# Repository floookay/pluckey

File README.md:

the pluckey is an ergodox like split keyboard with more pronounced columnal stagger and a vertical space key.  

I took inspiration from splitkbs Kyria and bishborias Ergodox design.

## layout

The following physical layouts are supported:  
  
And this is the default keymap as of now:  
  
[Keyboard-Layout-Editor](http://www.keyboard-layout-editor.com/#/gists/13c9d00bd0c0c9e3fe3b3d8d98672ef9) [(raw)](https://gist.github.com/floookay/13c9d00bd0c0c9e3fe3b3d8d98672ef9)

## pcb

The pcb is reversible and supports pcb mount MX style switches.  
It was designed using KiCAD and the following external libaries: [keebio-parts](https://github.com/keebio/Keebio-Parts.pretty) and [foostans kbd library](https://github.com/foostan/kbd)  
In order to assemble a pair you'll need the following hardware:

| amount | part                 | description             |
|--------|----------------------|-------------------------|
| 66/68  | key switches         | MX style                |
| 66/68  | diodes               | SMD or THT 1N4148(W)    |
| 2      | mini USB ports       | MX-54819-0519           |
| 2      | TRRS jacks           |                         |
| 2      | tact switch          |                         |
| 2      | pro micros           |                         |
| 2      | micro usb connectors | or two micro usb cables |
| 8      | short wires          |                         |

Additionally I'd recommend getting a pair of hotswapable headers for both pro micros.

**assembly:**  
Start by soldering the diodes, the headers, trrs jack and the mini usb port to the same side of the pcb. Make sure to clip the pins beforehand so they're flush on the other side.  
Now you can align your plate and solder in the switches.  
Plug the micro usb connector into the pro micro and align it according to the pinout on the solder mask. Depending on which headers you chose you might want to add electrical tape to the pro micro that's upside down so it doesnt touch the switch pins. Also nothe that you might have to solder on the controller at an angle if you're going with the default headers in order to be able to plug in the usb cable.  
Solder the wires to the micro usb connector (or cut open your existing cables) and solder the other side to the port headers according to the pinout on the solder mask.

<details>
<summary>more pictures</summary>

</details>
<br>

## case

### monolith

The monolith case is a tray mounted design and 3d printable in two pieces: case and (optional) plate  
It was designed using FreeCAD (and some SolidPython until it got too complex for me) so please feel free to configure the case to your liking. It's fairly parametric set up so depending on what you want to achieve you'll have a few starting points.
In order to assemble the case you'll need the following additional hardware:

| amount | part                 |
|--------|----------------------|
| 8      | M2 4mm screws        |
| 8      | M2 4mm spacers       |
| 8+     | rubber feet          |

**assembly:**  
After you soldered the PCB you can assemble the case. At first you're going to have to merge the spacers with the posts of the case. To do this heat up your soldering iron, position a spacer with a tweezer and press the spacer down with the tip of your soldering iron (make sure it's clean before this step). Do this with the other spacers, align the plate and pcb and fixate it with the screws. Lastly you can add the rubber feet according to your liking.

<details>
<summary>more pictures</summary>

</details>
<br>

### skeleton

The skeleton case is a simple open case for the pluckey pcb.  
The FreeCAD models are included in case you want to adjust the angle for example.  
All you need to do to assemble this case is to clip in the PCB. All you need to do to assemble this case is to clip in the PCB. If you're using encoders you'll have to cut the pins flush.

<details>
<summary>more pictures</summary>

</details>
<br>

### sandwich

The sandwich case is a laser cut acrylic case for the pluckey pcb from 3mm thick layers.
I also built this with FreeCAD so feel free to adjust. The kerf of the files is set to 0.2mm so you might need to adjust that.

| amount | part                                            |
|--------|-------------------------------------------------|
| 32     | M2 5+mm screws                                  |
| 1      | set of cylindrical M2 standoffs (male + female) |
| 4      | diode legs                                      |
| 8+     | rubber feet                                     |

**assembly:**  
After you soldered the components to the PCB you can start soldering the switches with the plate in between. If you want to use a rotary encoder you'll have to enlargen the hole slightly with a dremel to fit its legs. As this is a 3mm plate I like to put small strips of cellular rubber vertically along the columns between the pcb and plate next to the switches. This prevents the switches from popping out of the plate. After you soldered the plate you can put screws in the top layer and gradually add the other layers, spacers and diode legs as soon as they fit. Use the male and female standoffs to create larger larger standoffs that fit each hole height (for the exact length opne „more pictures“). Lastly add the rubber feet, make sure that you place them at the same distance from the edge of each step.

<details>
<summary>more pictures</summary>

</details>
<br>

## plate

If you want to print and use a plate I'd suggest you print the tolerance tester first (and maybe decrease the tolerances a bit).  
After you know the right margin for your printer you can adjust it in the plate model and export your plate in the desired layout.

## firmware

[QMK firmware](https://github.com/floookay/qmk_firmware/tree/master/keyboards/pluckey)

Compiling the keyboard (after setting up your build environment):

    make pluckey:default

Flashing the firmware:

    make pluckey:default:flash

## misc

> What where your goals behind designing this keyboard?

One thing I wanted to improve/avoid were keys that needed to be stabilized but at the same time have wider space keys to rest my thumbs on.

Another thing I wanted to achieve with this design was to be fairly flexible in terms of keycaps that can be used.  
Personally, I like the wider ergodox style modifier keys but keycap compability is unfortunatelly not that great beyond blank uniform caps.  
That's why I made the PCB compatible with all 1u keycaps that are offered in ortho keycap sets.

> What's next?

~~An acrylic sandwich-style case variants.~~  
I'm also thinking about making a pcb variant for low profile Choc switches with choc spacing.  

> What's the story behind the name?

I named the keyboard Pluckey after one of my favorite Animal Crossing villagers „Plucky“. The first letter of the logo represents Pluckys eye.

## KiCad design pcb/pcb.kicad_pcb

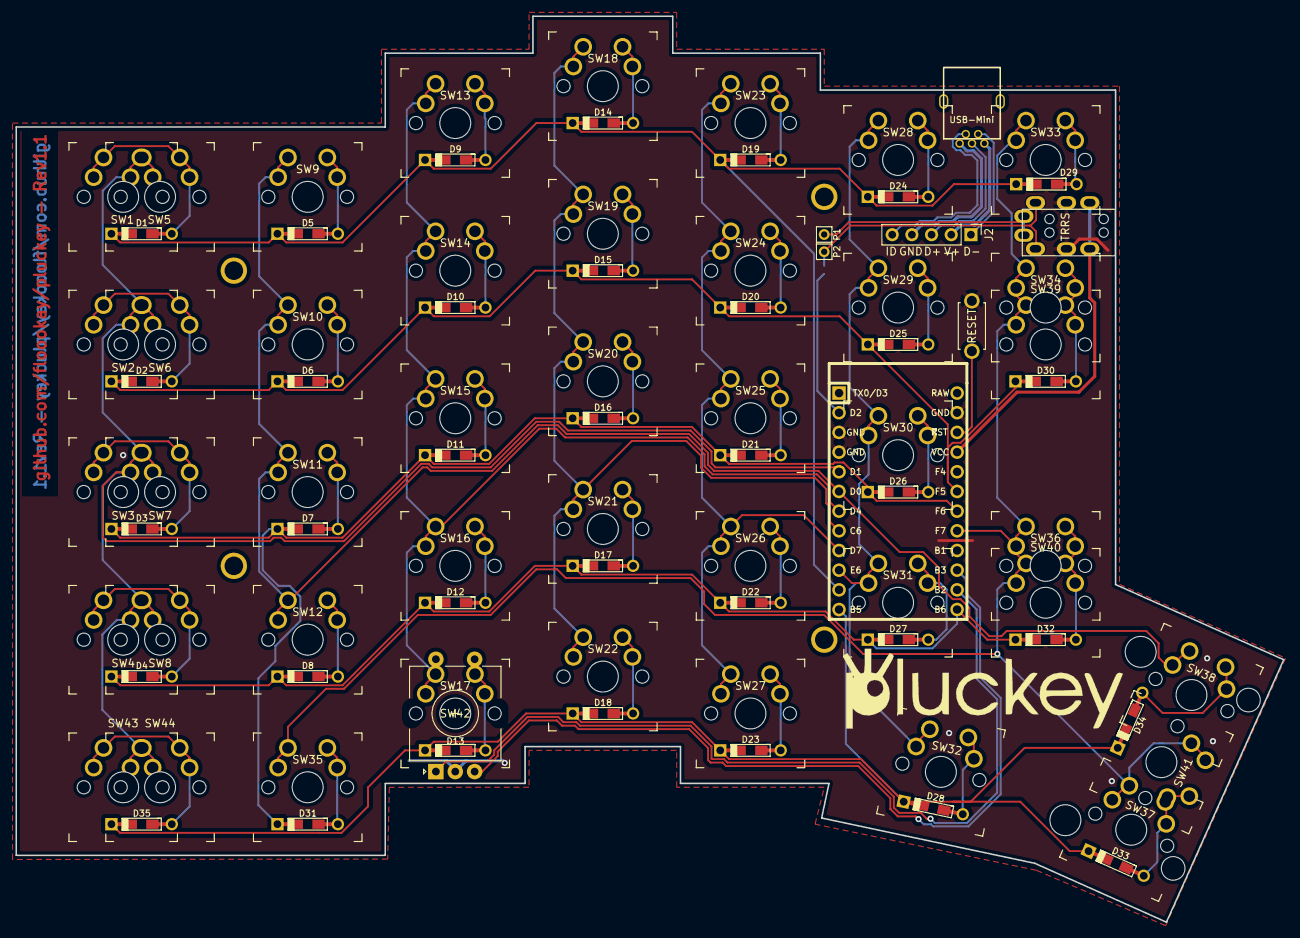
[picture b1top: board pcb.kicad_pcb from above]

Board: 2 copper layers, 163.6 x 116.9 mm, 91 parts (1 on the bottom side), 60 nets.

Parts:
D1, D2, D3, D4, D5, D6, D7, D8, D9, D10, D11, D12, D13, D14, D15, D16, D17, D18, D19, D20, D21, D22, D23, D24, D25, D26, D27, D28, D29, D30, D31, D32, D33, D34, D35: D; Diode-dual
H1, H2, H3, H4: MountingHole; m2.4_hole_plated
J1: USB-Mini; USB-Mini-B_2leg
J2: Conn_01x05; PinHeader_1x05_P2.54mm_Vertical
JP1: Jumper; JPC2
P1: i2c-pin1; 1pin_conn
P2: i2c-pin2; 1pin_conn
RSW1: SW_PUSH; ResetSW
SW1, SW2, SW3, SW4, SW5, SW6, SW7, SW8, SW9, SW10, SW11, SW12, SW13, SW14, SW15, SW16, SW17, SW18, SW19, SW20, SW21, SW22, SW23, SW24, SW25, SW26, SW27, SW28, SW29, SW30, SW31, SW32, SW33, SW34, SW35, SW36, SW37, SW38, SW39, SW40, SW41, SW43, SW44: SW_Push; SW_MX_reversible
SW42: Rotary_Encoder_Switch; RotaryEncoder_Alps_EC11E-Switch_Vertical_H20mm
U1: ProMicro; ArduinoProMicro
U2: TRRS; MJ-4PP-9

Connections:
/col0: SW1.2, SW2.2, SW3.2, SW4.2, SW5.1, SW6.1, SW7.1, SW8.1, SW43.2, SW44.1, U1.5 (2/PD1)
/col1: SW9.1, SW10.1, SW11.1, SW12.1, SW38.1, U1.6 (3/PD0)
/col2: SW13.1, SW14.1, SW15.1, SW16.1, SW17.1, SW42.S2, U1.7 (4/PD4)
/col3: SW18.1, SW19.1, SW20.1, SW21.1, SW22.1, U1.8 (5/PC6)
/col4: SW23.1, SW24.1, SW25.1, SW26.1, SW27.1, U1.9 (6/PD7)
/col5: SW28.1, SW29.1, SW30.1, SW31.1, SW32.1, U1.10 (7/PE6)
/col6: SW33.1, SW34.1, SW35.1, SW36.1, SW37.1, SW39.1, SW40.1, SW41.1, U1.17 (A0/PF7)
/data: JP1.1, U1.2 (RX1/PD2)
/re0: SW42.B, U1.15 (14/PB3)
/re1: SW42.A, U1.14 (16/PB2)
/reset: RSW1.1, U1.22 (RST)
/row0: D1.1 (K), D5.1 (K), D9.1 (K), D14.1 (K), D19.1 (K), D24.1 (K), D29.1 (K), U1.11 (8/PB4)
/row1: D2.1 (K), D6.1 (K), D10.1 (K), D15.1 (K), D20.1 (K), D25.1 (K), D30.1 (K), U1.19 (A2/PF5)
/row2: D3.1 (K), D7.1 (K), D11.1 (K), D16.1 (K), D21.1 (K), D26.1 (K), D31.1 (K), U1.18 (A1/PF6)
/row3: D4.1 (K), D8.1 (K), D12.1 (K), D17.1 (K), D22.1 (K), D27.1 (K), D32.1 (K), U1.13 (10/PB6)
/row4: D13.1 (K), D18.1 (K), D23.1 (K), D28.1 (K), D33.1 (K), D34.1 (K), D35.1 (K), U1.12 (9/PB5)
GND: RSW1.2, SW42.C, U1.3 (GND), U1.4 (GND), U1.23 (GND), U2.3 (RING1)
unnamed: D1.2 (A), SW1.1, SW5.2
unnamed: D2.2 (A), SW2.1, SW6.2
unnamed: D3.2 (A), SW3.1, SW7.2
unnamed: D4.2 (A), SW4.1, SW8.2
unnamed: D5.2 (A), SW9.2
unnamed: D6.2 (A), SW10.2
unnamed: D7.2 (A), SW11.2
unnamed: D8.2 (A), SW12.2
unnamed: D9.2 (A), SW13.2
unnamed: D10.2 (A), SW14.2
unnamed: D11.2 (A), SW15.2
unnamed: D12.2 (A), SW16.2
unnamed: D13.2 (A), SW17.2, SW42.S1
unnamed: D14.2 (A), SW18.2
unnamed: D15.2 (A), SW19.2
unnamed: D16.2 (A), SW20.2
unnamed: D17.2 (A), SW21.2
unnamed: D18.2 (A), SW22.2
unnamed: D19.2 (A), SW23.2
unnamed: D20.2 (A), SW24.2
unnamed: D21.2 (A), SW25.2
unnamed: D22.2 (A), SW26.2
unnamed: D23.2 (A), SW27.2
unnamed: D24.2 (A), SW28.2
unnamed: D25.2 (A), SW29.2
unnamed: D26.2 (A), SW30.2
unnamed: D27.2 (A), SW31.2
unnamed: D28.2 (A), SW32.2
unnamed: D29.2 (A), SW33.2
unnamed: D30.2 (A), SW34.2, SW39.2
unnamed: D31.2 (A), SW35.2
unnamed: D32.2 (A), SW36.2, SW40.2
unnamed: D33.2 (A), SW37.2, SW41.2
unnamed: D34.2 (A), SW38.2
unnamed: D35.2 (A), SW43.1, SW44.2
unnamed: J1.1 (VBUS), J2.2
unnamed: J1.2 (D-), J2.1
unnamed: J1.3 (D+), J2.3
unnamed: J1.4 (ID), J2.5
unnamed: J1.5 (GND), J2.4
unnamed: JP1.2, P2.1, U2.2 (TIP)
unnamed: P1.1, U2.1 (SLEEVE)
VCC: U1.21 (VCC), U2.4 (RING2)

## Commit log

2021-04-04 added description and sketch
2021-04-05 merged readmes
2021-04-05 added solidpython test
2021-04-05 added basic plate generator functions
2021-04-06 renamed case file
2021-04-06 added space key with adjustable angle
2021-04-09 added thumb cluster and fillings
2021-04-09 finished basic plate files
2021-04-10 fixed cap rendering
2021-04-11 added rotary encoder support
2021-04-11 increased middle finger stagger
2021-04-18 reworked holes
2021-04-24 added first version of the case
2021-04-24 added ergo plate dxf
2021-04-30 added alpha pcb files
2021-05-01 finished case and pcb prototype
2021-05-01 renamed the project
2021-05-02 added assembly instructions
2021-05-13 finalised pcb rev1.1
    added support for an encoder
    added support for a stablized 2u key on the double thumb keys
2021-05-21 reworked case with adjustable play between caps and walls
    (bottom plate missing)
2021-05-21 restructered case folder
2021-05-22 added skeleton case files
2021-05-23 updated silkscreen text
2021-05-25 updated skeleton model
2021-05-25 ignored gcode files
2021-05-25 fixed pin header footprint
2021-05-26 reworked monolith case
2021-05-27 added finishing touches to case
    - updated the case height so switches dont show
    - made mounting posts conical for better support
    - slightly adjusted port cutout height
    - added a hole in the bottom for the reset switch
2021-05-27 increased post hole size slightly
2021-05-28 added an optional bottom plug with the pluckey logo
    If you're wondering why: a small test print got stuck so hard on the mat
    that I ripped a hole into it. Exactly in the middle of the printing bed… fml
2021-05-28 took height of pro micro into account at a cone post
2021-05-29 updated gerbers
2021-06-19 reworked plate files
2021-06-19 added pictures to readme
2021-06-19 init sandwich case
2021-06-19 fixed image link to inside picture
2021-06-19 added a license
2021-06-26 fixed summary
2021-06-26 added missing via…
2021-06-26 added rotary encoder support notice
2021-07-04 added first few layers
2021-07-04 added vector ergo plate file
2021-07-04 moved plate file
2021-07-17 finished basic case form
2021-07-23 finished laser cut case files
2021-07-23 updated readme with sandwich case info
2021-07-24 added second top layer
2021-07-24 fixed typo
2021-08-14 fixed typos
2021-09-11 increased clearance for spacers, simplified needed components for assembly
2021-10-02 added fillet to layers
2021-10-02 updated 2d files
2021-10-02 updated readme with sandwich case details & pics
2021-10-23 Updated sandwich case pictures
2022-01-28 added kicad 6 backup folder
2022-01-28 added a key and moved a inner key for 5x7
